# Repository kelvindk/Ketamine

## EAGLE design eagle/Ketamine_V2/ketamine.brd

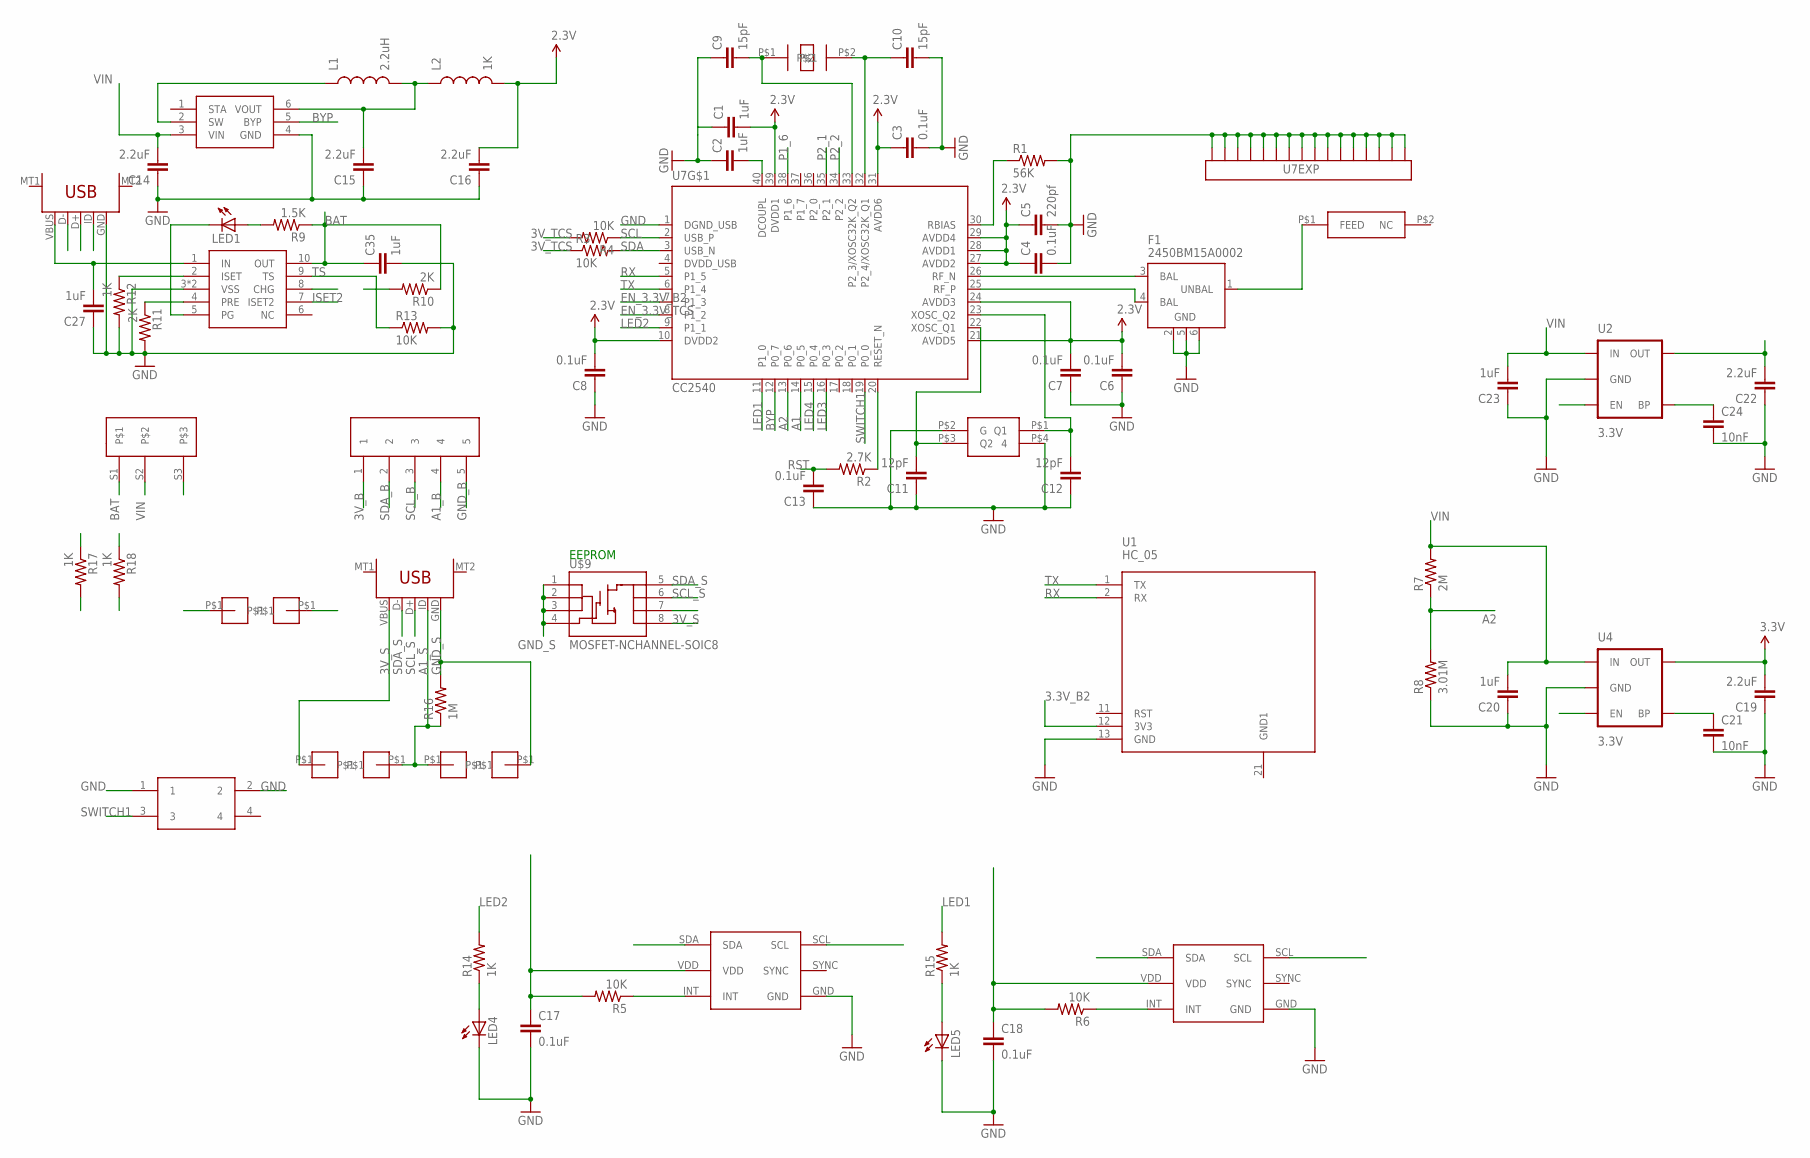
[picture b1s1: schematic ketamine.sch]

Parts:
C1, C2, C20, C23, C27, C35: 1uF; 0402-CAP
C3, C4, C6, C7, C8, C13, C17, C18: 0.1uF; 0402-CAP
C5: 220pf; 0402-CAP
C9, C10: 15pF; 0402-CAP
C11, C12: 12pF; 0402-CAP
C14, C15, C16, C19, C22: 2.2uF; 0402-CAP
C21, C24: 10nF; 0402-CAP
F1: 2450BM15A0002
L1: 2.2uH; 0805
L2: 1K; C0402
LED1, LED4, LED5: LED0603; LED-0603
R1: 56K; 0402-RES
R2: 2.7K; 0402-RES
R3, R4, R5, R6, R13: 10K; 0402-RES
R7: 2M; 0402-RES
R8: 3.01M; 0402-RES
R9: 1.5K; 0402-RES
R10, R11: 2K; 0402-RES
R12, R14, R15, R17, R18: 1K; 0402-RES
R16: 1M; 0402-RES
S1: SK12C0405
S2: SWITCH_SMD_6X6; 6X6MM
U1: HC_05; BLUETOOTH_SMD
U2, U4: 3.3V; SOT23-5
U5, U6: TCS3414CS; CHIPSCALE6
U7: CC2540; QFN40-6X6
U$1: 2450AT42A100
U$2: FA128
U$3: ST3215SB
U$4: TPS62730
U$8: MICRO_USB_PLUG
U$9: MOSFET-NCHANNEL-SOIC8; SO08
U$10, U$11, U$12, U$13, U$14, U$15: 5X3PAD
U$23: BQ24040; WSON-10
X1, X2: USB_MICROB_RECEPT; USB-MICROB

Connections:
2.3V: C1.2, C3.1, C4.1, C5.1, C6.2, C7.2, C8.2, C16.2, L2.2, U7.10 (DVDD2), U7.21 (AVDD5), U7.24 (AVDD3), U7.27 (AVDD2), U7.28 (AVDD1), U7.29 (AVDD4), U7.31 (AVDD6), U7.39 (DVDD1)
3.3V_B2: C19.2, U1.12 (3V3), U4.5 (OUT)
3V_B: U$8.1
3V_S: U$9.8 (D), U$14.P$1, X2.VBUS
3V_TCS: C17.1, C18.1, C22.2, R3.1, R4.2, R5.2, R6.2, U2.5 (OUT), U5.VDD, U6.VDD
A1: U7.14 (P0_5)
A1_B: U$8.4
A1_S: R16.1, U$10.P$1, U$15.P$1, X2.ID
A2: R7.1, R8.2, U7.13 (P0_6)
BAT: C35.1, R9.1, R10.1, S1.S1, U$23.10 (OUT)
BYP: U7.12 (P0_7), U$4.5 (BYP)
DVDD_USB: U7.4 (DVDD_USB)
EN_3.3V_B2: U4.3 (EN), U7.7 (P1_3)
EN_3.3V_TCS: U2.3 (EN), U7.8 (P1_2)
GND: C1.1, C2.1, C3.2, C4.2, C5.2, C6.1, C7.1, C8.1, C9.1, C10.2, C11.1, C12.1, C13.1, C14.1, C15.1, C16.1, C17.2, C18.2, C19.1, C20.1, C21.2, C22.1, C23.1, C24.2, C27.1, C35.2, F1.2 (GND), F1.5 (GND), F1.6 (GND), LED4.C, LED5.C, R1.2, R8.1, R11.2, R12.2, R13.2, S2.1, S2.2, U1.13 (GND), U2.2 (GND), U4.2 (GND), U5.GND, U6.GND, U7.1 (DGND_USB), U7.EXP@1 (EXP16), U7.EXP@2 (EXP16), U7.EXP@3 (EXP16), U7.EXP@4 (EXP16), U7.EXP@5 (EXP16), U7.EXP@6 (EXP16), U7.EXP@7 (EXP16), U7.EXP@8 (EXP16), U7.EXP@9 (EXP16), U7.EXP@10 (EXP16), U7.EXP@11 (EXP16), U7.EXP@12 (EXP16), U7.EXP@13 (EXP16), U7.EXP@14 (EXP16), U7.EXP@15 (EXP16), U7.EXP@16 (EXP16), U$2.P$2 (G), U$2.P$4 (4), U$4.4 (GND), U$23.3 (VSS), U$23.PAD (VSS), X1.GND
GND_B: U$8.5
GND_S: R16.2, U$9.1 (S), U$9.2 (S), U$9.3 (S), U$9.4 (G), U$9.7 (D), U$11.P$1, X2.GND
INT: R5.1, U5.INT
INT1: R6.1, U6.INT
ISET2: U$23.7 (ISET2)
LED1: R15.2, U7.11 (P1_0)
LED2: R14.2, U7.9 (P1_1)
LED3: R17.2, U7.16 (P0_3)
LED4: R18.2, U7.15 (P0_4)
unnamed: R1.1, U7.30 (RBIAS)
unnamed: C21.1, U4.4 (BP)
unnamed: F1.3 (BAL), U7.26 (RF_N)
unnamed: F1.4 (BAL), U7.25 (RF_P)
unnamed: C2.2, U7.40 (DCOUPL)
unnamed: C9.2, U7.33 (P2_3/XOSC32K_Q2), U$3.P$1
unnamed: C24.1, U2.4 (BP)
unnamed: C11.2, U7.22 (XOSC_Q1), U$2.P$3 (Q2)
unnamed: C12.2, U7.23 (XOSC_Q2), U$2.P$1 (Q1)
unnamed: C10.1, U7.32 (P2_4/XOSC32K_Q1), U$3.P$2
unnamed: L1.1, U$4.2 (SW)
unnamed: C15.2, L1.2, L2.1, U$4.6 (VOUT)
unnamed: F1.1 (UNBAL), U$1.P$1 (FEED)
unnamed: R2.1, U7.20 (RESET_N)
unnamed: LED1.C, U$23.5 (PG)
unnamed: LED1.A, R9.2
unnamed: LED4.A, R14.1
unnamed: LED5.A, R15.1
unnamed: R11.1, U$23.4 (PRE)
unnamed: R12.1, U$23.2 (ISET)
P1_6: U7.38 (P1_6)
P2_1: U7.35 (P2_1), X1.D+
P2_2: U7.34 (P2_2), X1.ID
RST: C13.2, R2.2, X1.D-
RX: U1.2 (RX), U7.5 (P1_5)
SCL: R4.1, U5.SCL, U6.SCL, U7.2 (USB_P)
SCL_B: U$8.3
SCL_S: U$9.6 (D), X2.D+
SDA: R3.2, U5.SDA, U6.SDA, U7.3 (USB_N)
SDA_B: U$8.2
SDA_S: U$9.5 (D), X2.D-
SWITCH1: S2.3, U7.19 (P0_0)
TS: R13.1, U$23.9 (TS)
TX: U1.1 (TX), U7.6 (P1_4)
VBUS: C27.2, U$23.1 (IN), X1.VBUS
VIN: C14.2, C20.2, C23.2, R7.2, S1.S2, U2.1 (IN), U4.1 (IN), U$4.3 (VIN)

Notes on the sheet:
EEPROM

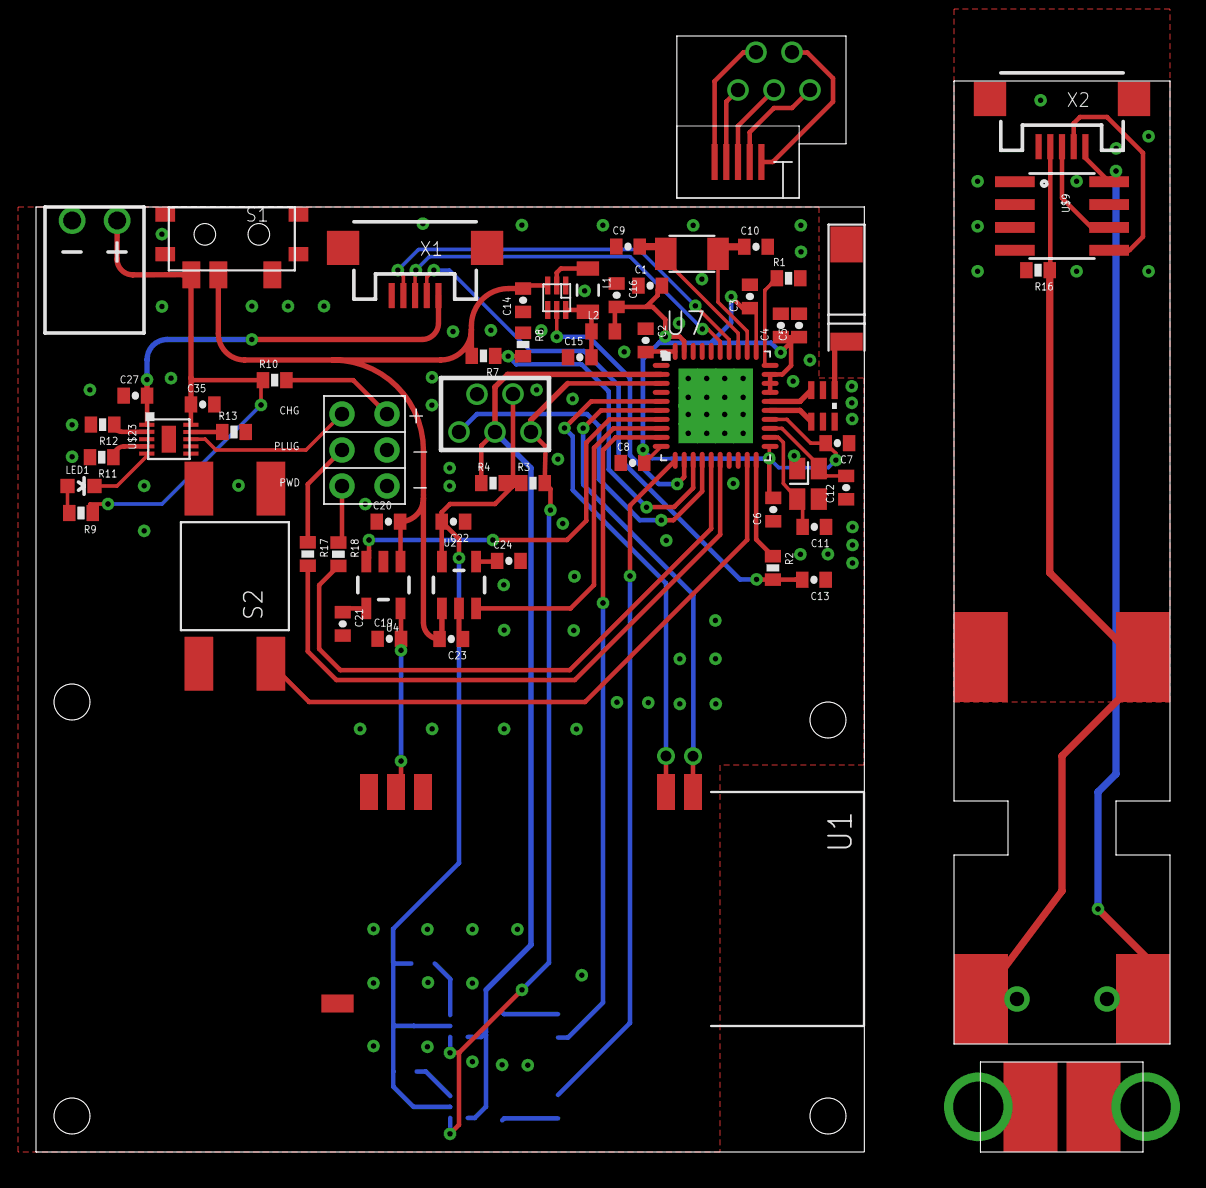
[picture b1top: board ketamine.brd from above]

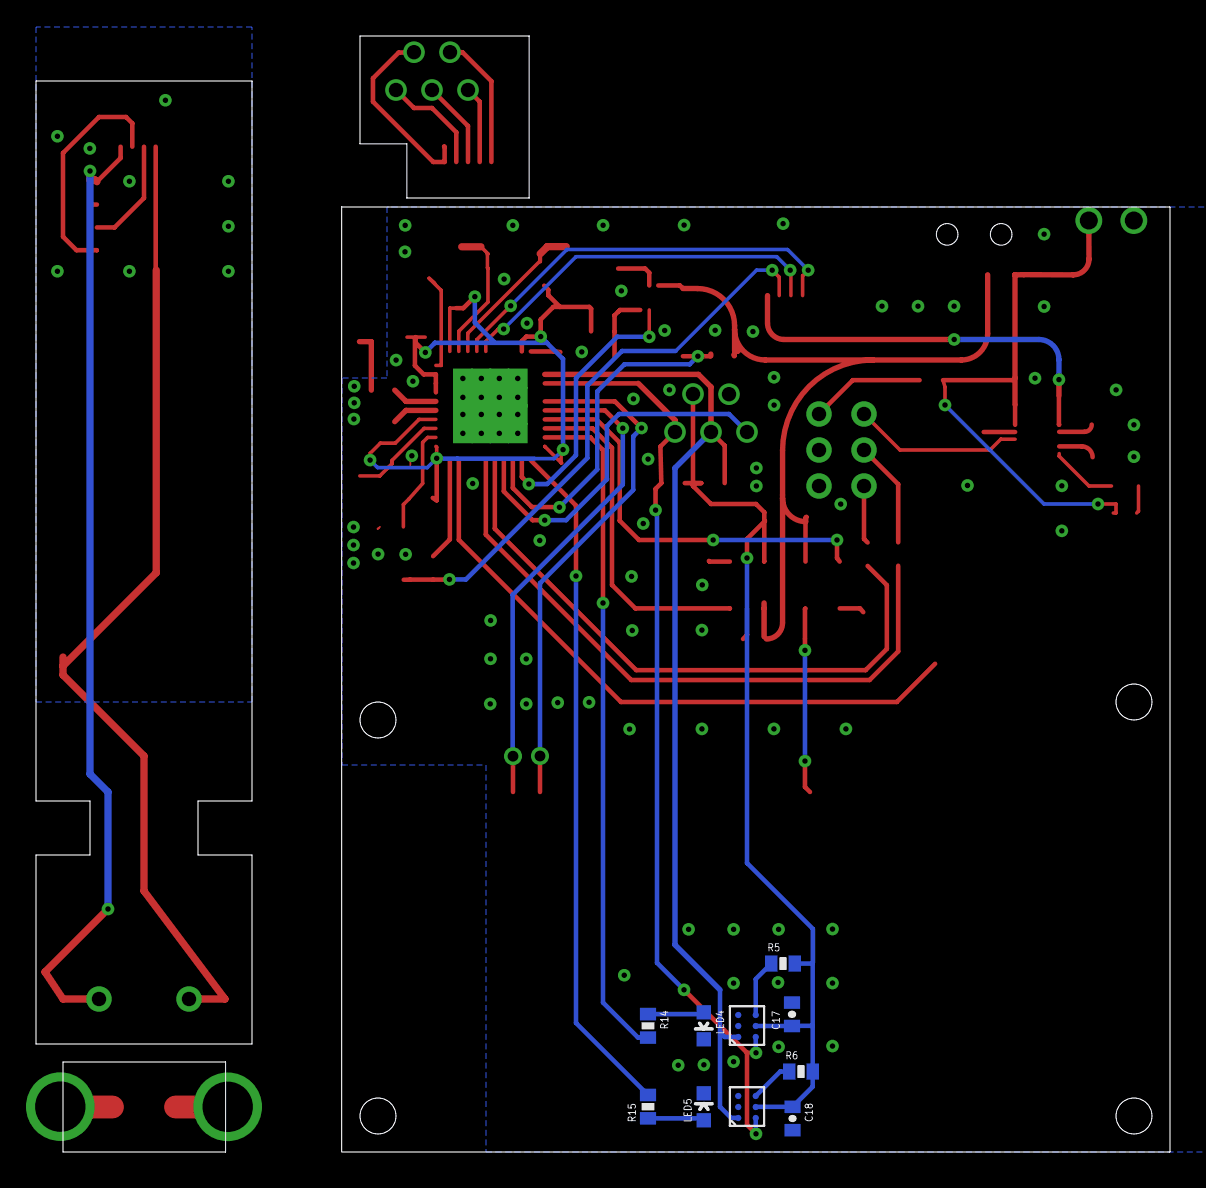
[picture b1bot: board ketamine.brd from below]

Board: 2 copper layers, 63.0 x 62.0 mm, 73 parts (10 on the bottom side), 51 nets.

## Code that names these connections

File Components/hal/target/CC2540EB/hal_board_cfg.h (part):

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
/* 1  */
#define LED1_BV                      BV(0)
#define LED1_SBIT                    P1_0
#define LED1_DDR                     P1DIR
#define LED1_POLARITY                ACTIVE_HIGH

  /* 2  */
#define LED2_BV                      BV(1)
#define LED2_SBIT                    P1_1
#define LED2_DDR                     P1DIR
#define LED2_POLARITY                ACTIVE_HIGH

  /* 3 */
#define LED3_BV                      BV(3)
#define LED3_SBIT                    P0_3
#define LED3_DDR                     P0DIR
#define LED3_POLARITY                ACTIVE_HIGH
  
  /* 3 */
#define LED4_BV                      BV(4)
#define LED4_SBIT                    P0_4
#define LED4_DDR                     P0DIR
#define LED4_POLARITY                ACTIVE_HIGH

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
/* S1 */
#define PUSH1_BV                       BV(0)
#define PUSH1_SBIT                     P0_0

#ifdef HAL_BOARD_CC2530EB_REV17
  #define PUSH1_POLARITY               ACTIVE_HIGH
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
/* XNV */

#define XNV_SPI_BEGIN()             st(P1_3 = 0;)
#define XNV_SPI_TX(x)               st(U1CSR &= ~0x02; U1DBUF = (x);)
#define XNV_SPI_RX()                U1DBUF
#define XNV_SPI_WAIT_RXRDY()        st(while (!(U1CSR & 0x02));)
#define XNV_SPI_END()               st(P1_3 = 1;)

// The TI reference design uses UART1 Alt. 2 in SPI mode.
#define XNV_SPI_INIT() \
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
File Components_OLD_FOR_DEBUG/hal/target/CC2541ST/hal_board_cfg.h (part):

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
/* 1 - D1 Green */
#define LED1_BV           BV(3)
#define LED1_SBIT         P0_3
#define LED1_DDR          P1DIR
#define LED1_POLARITY     ACTIVE_LOW

/* 2 - D2 Green */
#define LED2_BV           BV(4)
#define LED2_SBIT         P0_4
#define LED2_DDR          P0DIR
#define LED2_POLARITY     ACTIVE_LOW

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
/* Gyro power */
#define GYRO_VDD_BV       BV(0)
#define GYRO_VDD_SBIT     P0_0
#define GYRO_VDD_DDR      P0DIR

/* Gyro interrupt */
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
/* Magnetometer interrupt */
#define MAG_INT_BV        BV(6)
#define MAG_INT_SBIT      P0_6
#define MAG_INT_DDR       P0DIR

/* DCDC control */
#define DCDC_BV           BV(7)
#define DCDC_SBIT         P0_7
#define DCDC_DDR          P0DIR
#define DCDC_SEL          P0SEL

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
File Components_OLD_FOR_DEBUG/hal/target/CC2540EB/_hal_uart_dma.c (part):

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#define PxIEN                      P1IEN
#define PxIFG                      P1IFG
#define PxIF                       P1IF
#define DMA_RDYIn                  P1_2
#define DMA_RDYOut                 P1_3
#define DMA_RDYIn_BIT              BV(2)        // Same as the I/O Select for CTS flow control.
#define DMA_RDYOut_BIT             BV(3)        // Same as the I/O Select for manual RTS flow ctrl.
// Falling edge ISR on P0 pins.
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#define PxIEN                      P1IEN
#define PxIFG                      P1IFG
#define PxIF                       P1IF
#define DMA_RDYIn                  P1_4
#define DMA_RDYOut                 P1_5
#define DMA_RDYIn_BIT              BV(4)        // Same as the I/O Select for CTS flow control.
#define DMA_RDYOut_BIT             BV(5)        // Same as the I/O Select for manual RTS flow ctrl.
// Falling edge ISR on P1.4-7 pins.
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
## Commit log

2015-04-03 add .gitignore
2015-04-03 modify .gitignore
2015-04-03 fixed untracked files
2015-04-06 original SimplePeripheralNotification project
2015-04-06 add i2c to Simple peripheral
2015-04-10 change HalAccSelect into HalTmpSelect and add tcs3424cs header
2015-04-11 add color sensor api into cc2541
2015-04-13 cc2541 with value of color sensor
2015-04-16 change file name to Ketamine; modified colorinit function to pass address argument
2015-04-16 it seems like workable with two color sensor and blink LEDs
2015-04-27 LED bug fixed
2015-04-29 add read/write eeprom function to cc2541
2015-04-29 add global state control
2015-04-29 temporary workable version with complete flow control
2015-05-01 Workable version_1 with complete flow control
2015-05-04 temperary commit for debug
2015-05-04 temporay commit for clor sensor debug
2015-05-04 workable in sleep mode
2015-05-05 fix color sensor bug and try alternate turn on color sensor.
2015-05-06 fix isConected bug
2015-05-08 some bugs in revision version
2015-05-08 modify periodical task
2015-05-11 fixed color bug during sleep mode
2015-05-11 Temporary commit for uart debug
2015-05-13 fixed broadcast bug
2015-05-14 solve eeprom write bug
2015-05-16 fixed global count bug
2015-05-17 Syncronize code for BT
2015-05-17 Experimental ver with a lot of bugs
2015-05-17 4 state color, with some bugs
2015-05-17 Strange behaviour in LEDs
2015-05-17 Add_UART
2015-05-18 color alternative read in 4 states version
2015-05-18 Short timer for read color delay
2015-05-20 Tricky method to avoid crash by placing eeprom_read after color_read
2015-05-20 Temporarorily fix write 4 command
2015-05-20 Fix write 4 bug by allowing delay.
2015-05-21 Temporary version for develop INT
2015-06-01 add eagle files to master
2015-06-15 Modify adc read pin
2015-06-15 update eagle files
2015-06-15 Modify threshold
2015-06-18 Add runnable uart componets
2015-06-18 modify .gitignore file and remove files created by cross platform
2015-06-20 Uart command finished version 1
2015-06-22 temporay uart get data without PM
2015-06-22 start Ack added
2015-06-23 Transmission without ack
2015-06-24 Picture transmission with Acks
2015-06-25 Repeated pic transmission finished
2015-06-25 Clear *.orig file
2015-06-30 UART_with_PM
2015-06-30 Turn on EEPROM regulator
2015-06-30 Turn on regulator for EEPROM
2015-07-02 bugs in INT
2015-07-02 solve LED problem oon confliction with UART
2015-07-03 Workable for slow transmission
2015-07-03 commit components
2015-07-06 Temporary commit for syncronize
2015-07-06 Add state 0x0A for displaying version
2015-07-08 Commit for INT debug
2015-07-08 Temporary add INT vesrion
2015-07-08 Temporary add INT vesrion1
2015-07-15 Add channel 6 for write ID function
2015-07-20 Add retransmission protocol
2015-07-21 Add botton control
2015-07-23 Commit for debug
2015-07-25 Dug in second picture transmission, state change to 1 after exception
2015-07-26 Version 5: fix retransmission bug for isLastPkt
2015-07-28 Version 8: Turn on Connection timeout for 5 minutes
2015-08-01 Fix bug on direct termination
2015-08-02 Version 11: Cancel FD FE header, fix stop timer bug, adjust led signal for low power
2015-08-02 Syncronize profile
2015-08-02 Syncronize for component
2015-08-02 Fix lowPowerCount for low power when wake up
2015-08-02 Close debug message
2015-08-02 Adjust low power threshold
2015-08-02 Version 12: Fixed lowPowerWarning mechanism
2015-08-06 Version 16: return state 1 after unplug case
2015-08-14 Version 17: Fix a retransmission bug.
2015-08-17 FIx cameraState at 0x30 might be trapped in dead lock problem
2015-09-06 Commit to modify camera mechanism.
2015-09-14 Vesion 20: Revised camera transmission.
2015-10-11 Commit for backup: branch debug, 2015/10/11.

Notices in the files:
Components/hal/target/CC2540EB/hal_board_cfg.h:
Copyright 2006-2013 Texas Instruments Incorporated. All rights reserved.
granted under the terms of a software license agreement between the user
Components_OLD_FOR_DEBUG/hal/target/CC2541ST/hal_board_cfg.h:
Copyright 2012  Texas Instruments Incorporated. All rights reserved.
parts and their libraries:
SparkFun: Licensing: CC v3.0 Share-Alike You are welcome to use this library for commercial purposes.
